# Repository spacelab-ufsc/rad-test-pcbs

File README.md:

<h1 align="center">
	RELIABILITY ENHANCED ELECTRICAL POWER SYSTEM (RE²PS) HARDWARE
	<br>
</h1>

<p align="center">

</p>

<details>
    <summary><b>Summary</b></summary>
    <ol>
        <li>
            <a href="#overview">Overview</a>
        </li>
        <li>
            <a href="#repository-organization">Repository Organization</a>
        </li>
        <li>
            <a href="#license">License</a>
        </li>
        <li>
            <a href="#releases">Releases</a>
        </li>
        <li>
            <a href="#notes">Notes</a>
        </li>
        <li>
            <a href="#references">References</a>
        </li>
    </ol>
</details>

## Overview
The PCB of **RE²PS** [[1]](#1) was designed to be more reliable than previous EPS models developed by SpaceLab. To achieve this, ECSS standards for PCB development in space environments were tailored for the project [[2]](#2). Some flexibility was applied in selecting new connectors for interfacing with other modules, but whenever possible, previously used connectors, such as Pico-Locks and PicoBlades, were chosen.

<!-- 

-->

<p align="center">

</p>

## Repository Organization
`sources`: Main files of the RE²PS's hardware project.

`outputs`: Output files, such as figures of the RE²PS's PCB, schematics, BOM and more.

## License
This project is open-source under the following license: CERN Open Hardware License v2.0.

## Releases

Releases are published after  ensuring that the project itself do not have any major errors and after testing the PCB. Please refer to the **documentation** for more details.

## Notes
For more info about the SpaceLab, access our [GitHub](https://github.com/spacelab-ufsc/spacelab), [Linkedin](https://br.linkedin.com/company/spacelab-ufsc) or our [website](https://spacelab.ufsc.br/en/home/).

## References
<a id="1">[1]</a> D. L. Figueiredo, "Reliability Enhanced Electrical Power System for Nanosatellites," in <i>Repositório Institucional da UFSC</i>, pp. 1-85, 2023, available at <a href="https://repositorio.ufsc.br/bitstream/handle/123456789/247559/PEEL2103-D.pdf?sequence=1&isAllowed=y"> this link</a>.

<a id="2">[2]</a> C. A. Rigo, L. O. Seman, M. D. Berejuck and E. A. Bezerra, "Printed Circuit Board Design Methodology for Embedded Systems Targeting Space Applications," in IEEE Latin America Transactions, vol. 18, no. 02, pp. 257-264, 2020, available at <a href="https://ieeexplore.ieee.org/document/9085278"> this link</a>.

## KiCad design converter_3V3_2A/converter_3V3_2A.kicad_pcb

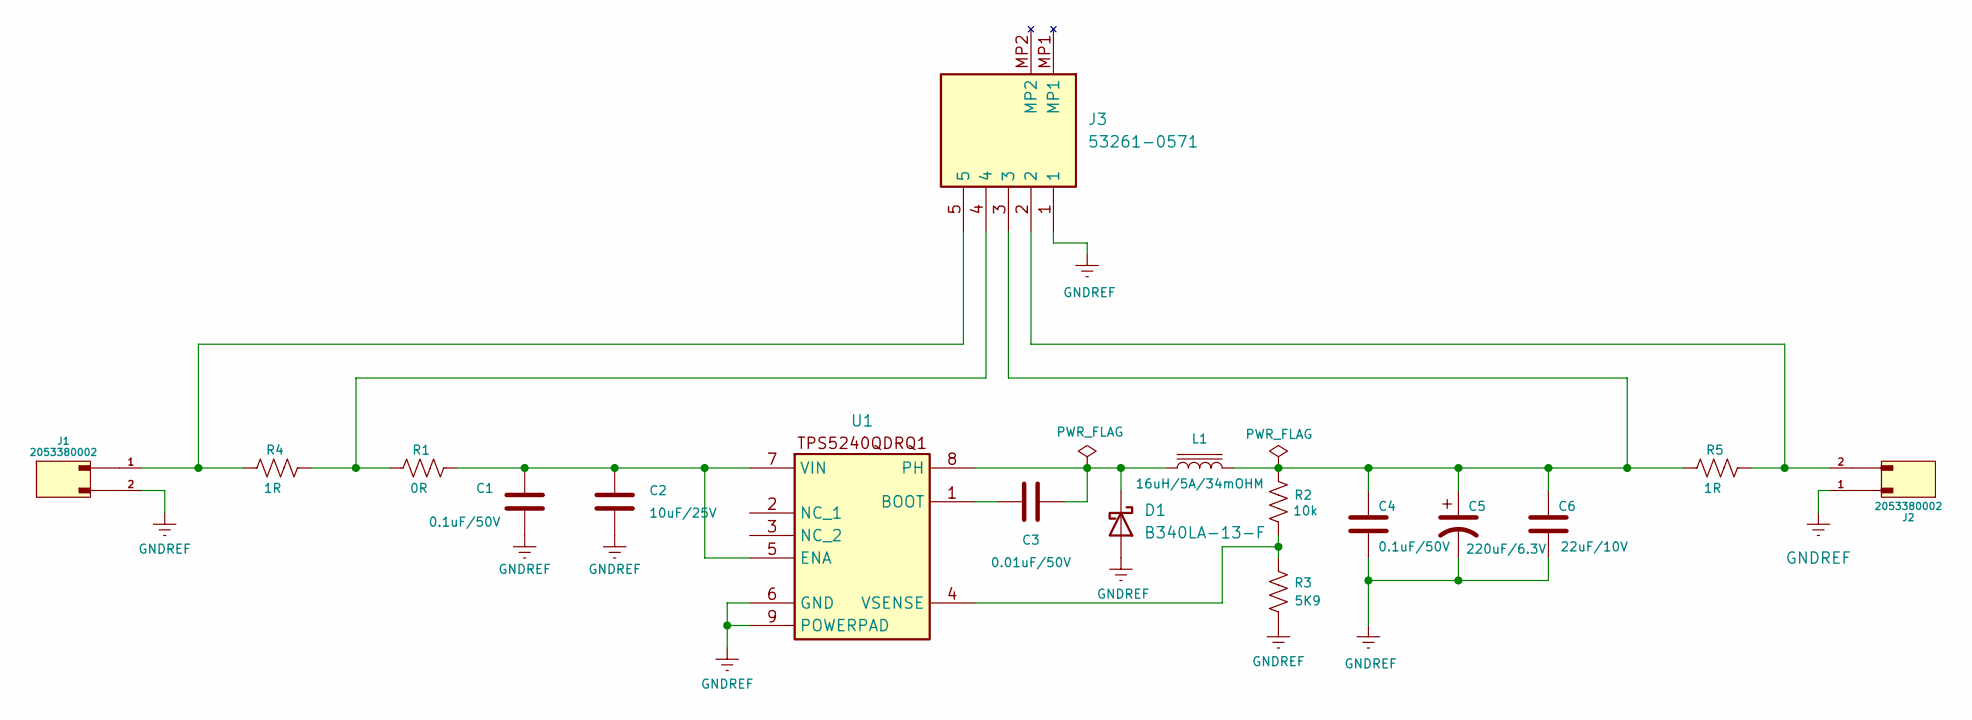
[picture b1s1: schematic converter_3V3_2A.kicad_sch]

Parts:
C1, C4: 0.1uF/50V; C_1206_3216Metric
C2: 10uF/25V; C_1206_3216Metric
C3: 0.01uF/50V; C_1206_3216Metric
C5: 220uF/6.3V; C_1206_3216Metric
C6: 22uF/10V; C_1206_3216Metric
D1: B340LA-13-F; DIOM5226X240N
J1, J2: 2053380002; MPN 2053380002
J3: 53261-0571; 532610571TR250; Mouser Part Number 538-53261-0571
L1: 16uH/5A/34mOHM; WE-HCI_105023
R1: 0R; R_0805_2012Metric_Pad1.20x1.40mm_HandSolder
R2: 10k; R_0805_2012Metric_Pad1.20x1.40mm_HandSolder
R3: 5K9; R_0805_2012Metric_Pad1.20x1.40mm_HandSolder
R4, R5: 1R; R_0805_2012Metric_Pad1.20x1.40mm_HandSolder
U1: TI_SO-PowerPAD-8

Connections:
GNDREF: C1.2, C2.2, C4.2, C5.2, C6.2, D1.2 (A), J1.2, J2.1, J3.1, R3.2, U1.6 (GND), U1.9 (POWERPAD)
unnamed: C4.1, C5.1, C6.1, J3.3, L1.2, R2.1, R5.1
unnamed: C3.2, D1.1 (K), L1.1, U1.8 (PH)
unnamed: J1.1, J3.5, R4.1
unnamed: J2.2, J3.2, R5.2
unnamed: J3.4, R1.1, R4.2
unnamed: C3.1, U1.1 (BOOT)
unnamed: C1.1, C2.1, R1.2, U1.5 (ENA), U1.7 (VIN)
unnamed: R2.2, R3.1, U1.4 (VSENSE)

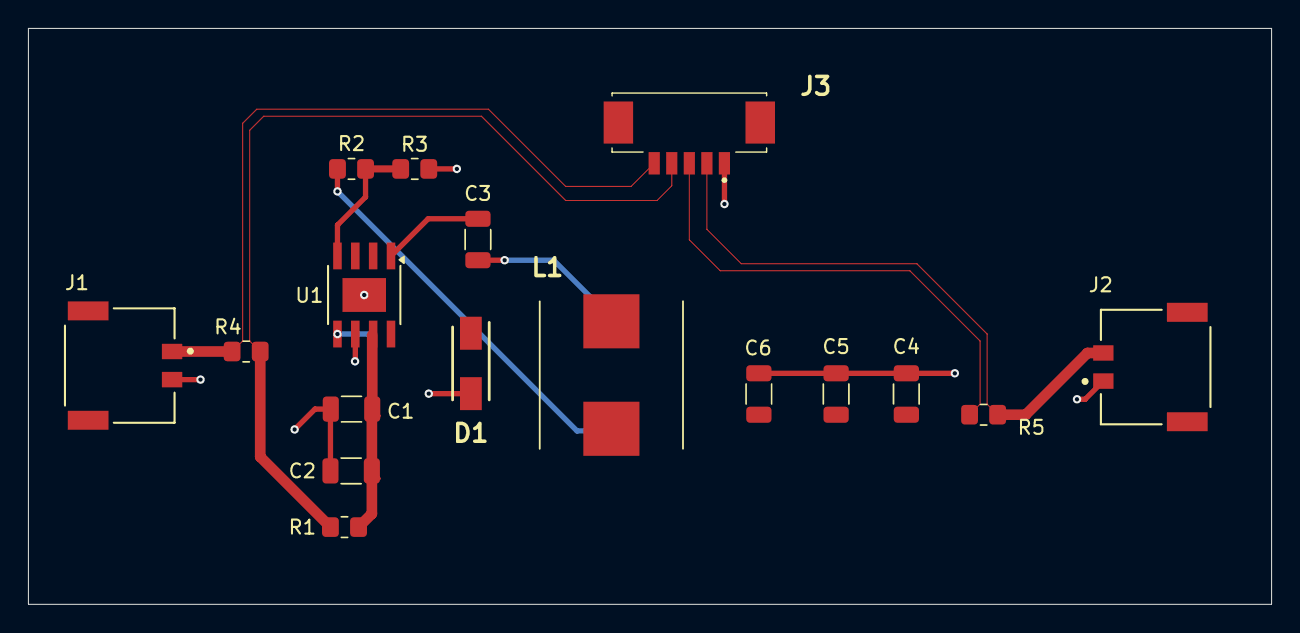
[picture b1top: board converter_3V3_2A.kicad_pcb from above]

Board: 2 copper layers, 88.5 x 41.0 mm, 17 parts (0 on the bottom side), 9 nets.

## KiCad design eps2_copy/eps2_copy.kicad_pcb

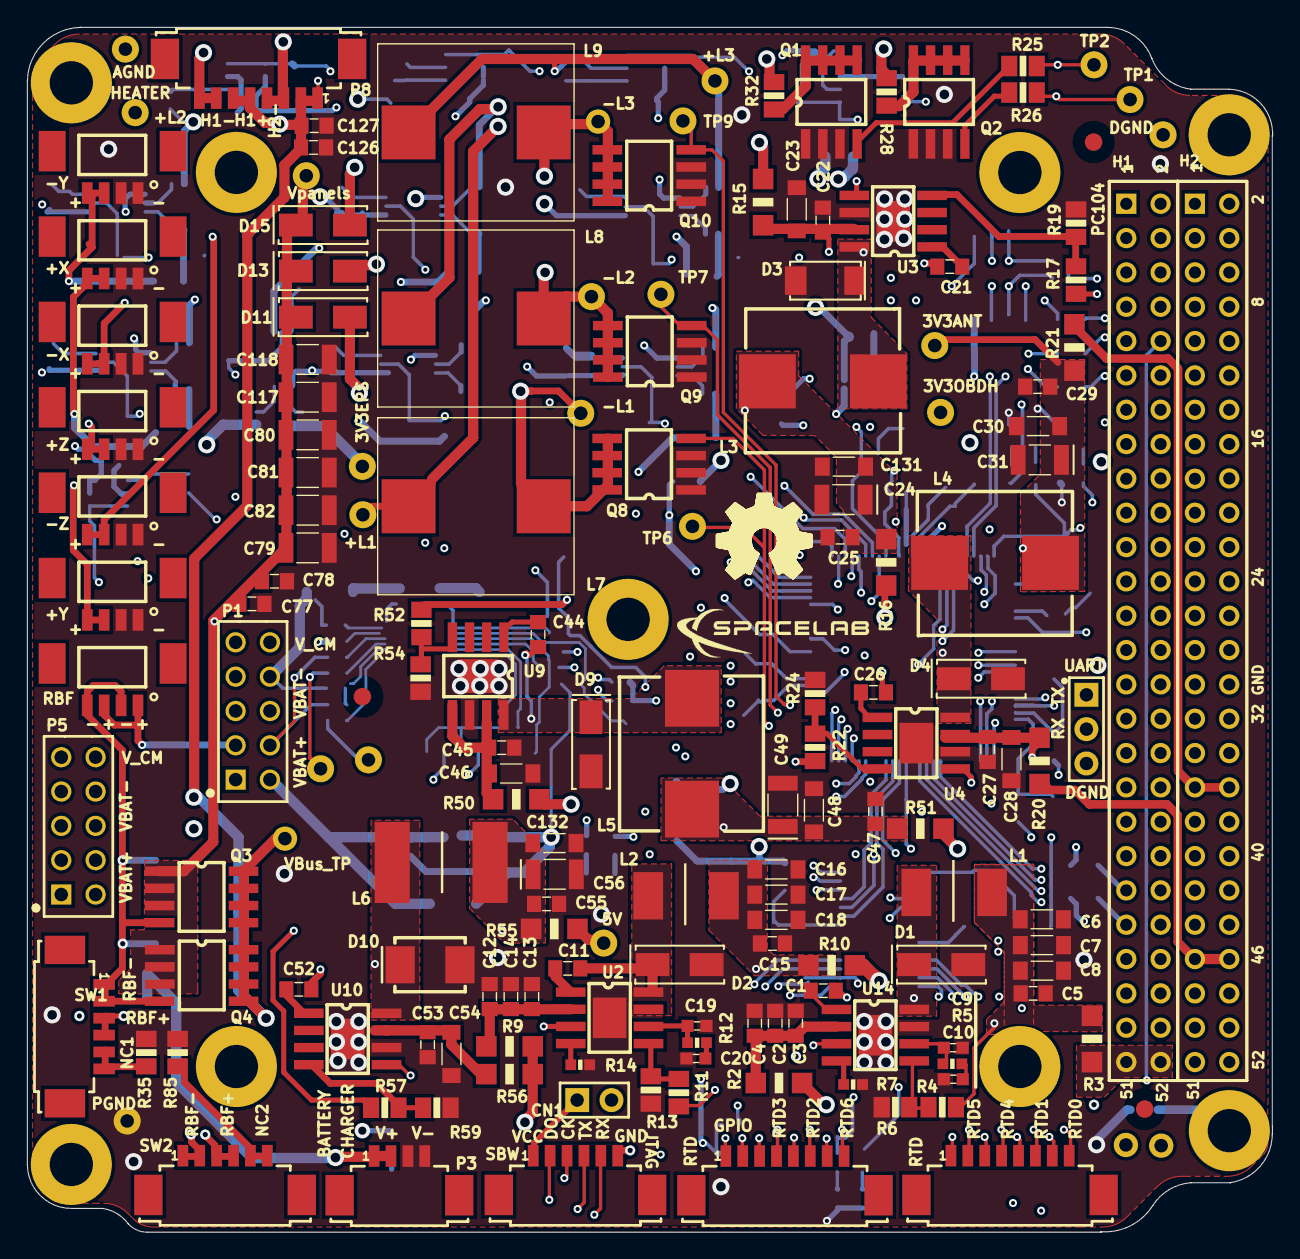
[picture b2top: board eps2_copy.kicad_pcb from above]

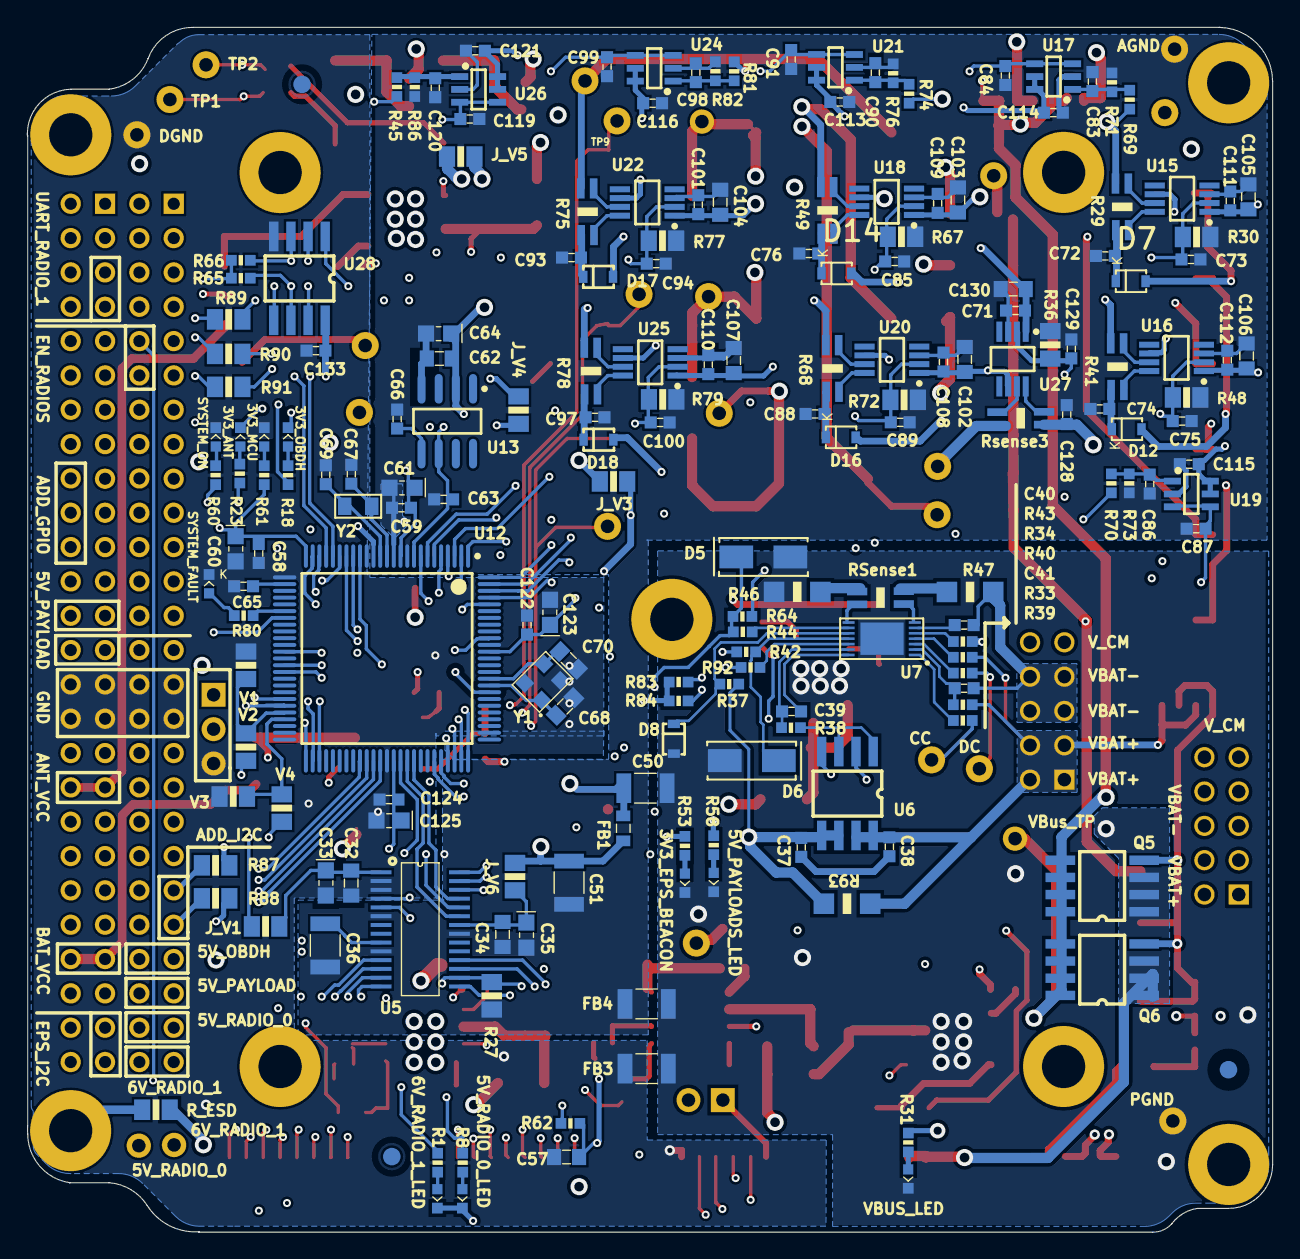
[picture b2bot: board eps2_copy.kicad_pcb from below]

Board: 4 copper layers, 92.1 x 89.1 mm, 362 parts (193 on the bottom side), 207 nets.

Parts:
3V3ANT, 3V3EPS, 3V3OBDH, 5V, 5V_RADIO_0, 6V_RADIO_1: TEST_POINT
3V3_ANT, 3V3_EPS_BEACON, 3V3_MCU, 3V3_OBDH, 5V_PAYLOADS_LED, 5V_RADIO_0_LED, 6V_RADIO_1_LED: DNP; 0603-LED
+L1, +L2, +L3: TEST_POINT
+X: Header 4_PicoBlade; HDR4 PicoBlade
+Y: Header 4_PicoBlade; HDR4 PicoBlade
+Z: Header 4_PicoBlade; HDR4 PicoBlade
-L1, -L2, -L3: TEST_POINT
-X: Header 4_PicoBlade; HDR4 PicoBlade
-Y: Header 4_PicoBlade; HDR4 PicoBlade
-Z: Header 4_PicoBlade; HDR4 PicoBlade
C1, C2, C5, C11, C12, C15, C22, C25, C27, C29, C45, C47, C53, C55, C62, C77, C78, C126, C127: 0.1uF/50V; CC0805
C3, C4, C13, C14, C102, C103, C104, C105, C106, C107, C130: 4.7uF/25V; CC0805
C6, C7, C8, C16, C17, C18, C30, C48, C131, C132: 22uF/10V; CC1206
C9, C19: 13pF/50V; CC0603
C10, C20: 5.6nF/100V; CC0603
C21, C26, C32, C34, C44, C52: 0.01uF/50V; CC0805
C23, C28, C46, C54: 10uF/25V; CC1206
C24, C31, C49, C56: 220uF/6.3V; cc1210
C33, C35, C60, C61, C64, C123, C125: 10uF/10V; CC0805_Tantalum
C36, C50, C51, C79, C80, C81, C82, C117, C118: 22uF/25V; CC1210
C37, C38: 1000pF/50V; CC0603
C39, C65: 0.47uF/50V; CC0603
C40, C41, C58, C59, C63, C71, C72, C73, C74, C75, C76, C83, C84, C85, C86, C87, C88, C89, C90, C91, C93, C94, C97, C98, C99, C100, C101, C108, C109, C110, C111, C112, C113, C114, C115, C116, C119, C120, C121, C122, C124, C128, C129, C133: 0.1uF/50V; CC0603
C57: 1nF/16V; CC0805
C66: 0.01uF/25V; CC0603
C67, C69: 12pF/50V; CC0603
C68, C70: 10pF/100V; CC0805
CC: TEST_POINT
CN1: 826646-2; HDR 1X2
D1, D2: FSV530AF; DO-214AC
D3: CMS06(TE12L,Q,M); cms06
D4, D9, D11, D13, D15: B340LA-13-F; DO-214AC
D5, D6: 3SMAJ5919B-TP; DO-214AC
D7, D8, D12, D14, D16, D17, D18: DNP; SOD323F
D10: B220-13-F; DO-214AA
DC: TEST_POINT
FB1: 30R@100Mhz, 3A; IND0805
FB3, FB4: 30R@100Mhz, 10A; IND1210
FD1, FD2, FD3, FD4, FD5, FD6: Fiducial 1.3; Fiducial 1.3mm
J_V1, J_V3, J_V4, J_V5, J_V6: 0R; 0805
L1, L2: 2.2uH/9A 15mOHM; Ind_SRP6540
L3: 27uH/4.3A/42.5mOHM; IND_744325xxx
L4, L5: 16uH/5A/34.5mOHM; IND_744325xxx
L6: 10uH/6.4A/51.8mOHM; Ind_IHLP
L7, L8, L9: 22uH/6.3/25.7mOHM; IND_HC9
MEC1, MEC2, MEC3, MEC4, MEC5, MEC6, MEC7, MEC8, MEC9: M3; M3 hole
P1, P5: Header 5X2IPS1-105-01-S-D; IPS1-105-01-S-D
P3: 0532610471; PICOBLADE 4PIN RIGHT ANGLE
P8: 0532610871; PICOBLADE 8PIN RIGHT ANGLE
PC104: PC104
Q1, Q2, Q8, Q9, Q10: MOSFET-N; SOIC8_Mosfet
Q3, Q4, Q5, Q6: MOSFET-P-SI4403CDY-T1-GE3; SOIC8_Mosfet
R1, R8, R18, R23, R31, R34, R37, R39, R40, R43, R53, R58, R60, R61: 1k; 0603
R2, R3, R9, R10, R15, R16, R20, R21, R46, R47, R50, R51, R55, R56, R93: 0R; 1206
R4: 75k; 0805
R5, R12: 19.6k; 0603
R6, R13: 11.5k; 0805
R7, R14: 140k; 0603
R11: 60.4k; 0805
R17, R22, R52, R57: 10k; 0805
R19, R24, R54: 5K9; 0805
R25, R26: 1k; 0805
R27: 1.65K; 0805
R28, R32, R87, R88, R89, R90, R91: 0R; 0805
R29, R41, R49, R68, R75, R78: 0.02R/0.5W; 1206 - ohmite
R30, R48, R67, R72, R77, R79: 3k3; R0805
R33, R42, R44: 150R; 0603
R35, R85: 100K 1/10W; 0805
R36: 4.02K; 0805
R38: 470R; 0603
R45, R70: 300K; 0603
R59: 3.24k 1/8W; 0805
R62: 47k; 0603
R64: 4K7; 0603
R65, R66, R83, R84: 10k; R0603
R69, R74, R81: 93K1; 0603
R71, R73, R76, R82, R86: 100K; 0603
R80: 1k; R0603
R92: 150R; R0603
RBF: 0533980471; PICOBLADE 4PIN VERTICAL
RSense1: 0.01R/0.5W; 1206 - ohmite
RTD1, RTD2: 0532610871; PICOBLADE 8PIN RIGHT ANGLE
R_ESD: 1.2M; 0805
Rsense3: 0.075R/0.5W; 1206 - ohmite
SBW: 0532610671; PICOBLADE 6PIN Right Angle
SW1, SW2: 0532610671; PICOBLADE 6PIN Right Angle
SYSTEM_FAULT: 150060RS75000; 0603-RED-LED
SYSTEM_ON: RED; 0603-LED
TP1, TP2, TP6, TP7, TP9: TEST_POINT
U2, U14: TPS54540QDDARQ1; SO8 Power PAD
U3: TPS5410QDRQ1; SO8 Power PAD
U4, U9: TPS5420QDRQ1; SO8 Power PAD
U5: ADS1248IPW; TSSOP28
U6: FDS6898AZ; SOIC8
U7: DS2777G+; TDFN-14-EP_3x5
U10: TPS5430QDDARQ1; SO8 Power PAD
U12: MSP430F6659IPZR; PZ0100A_N
U13: REF5025AQDRQ1; SOIC-8
U15, U16, U18, U20, U22, U25, U27: MAX9934TAUA+; MSOP-8
U17, U19, U21, U24, U26: TLV341AIDBVR; SOT-23 6L
U28: TCA4311ADR; SOIC8
UART: DNP; HDR 1X3
V1, V2, V3, V4: 47k; 0805
VBUS_LED: DNP; 0603-LED
VBus_TP: TEST_POINT
Vpanels: TEST_POINT
Y1: 32MHz 10ppm; XTAL_ABM8X
Y2: 32.768kHz 12.5pF; ABS06 0805

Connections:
3V3_DEPLOYMENT_ANT: PC104.H2-35, PC104.H2-36, R21.1
3V3_EPS_BEACON: 3V3EPS.1, C50.1, FB1.1, J_V1.2, J_V3.2, PC104.H2-27, PC104.H2-28, Rsense3.2
3V3_HEATER: C32.1, C33.1, J_V1.1, U5.1
3V3_M: C71.2, C101.2, C102.1, C103.1, C104.1, C105.1, C106.1, C107.1, C108.2, C109.2, C110.2, C111.2, C112.2, C113.2, C114.2, C115.2, C116.2, C121.2, C130.1, J_V5.1, U15.1, U15.6, U16.1, U16.6, U17.5, U17.6, U18.1, U18.6, U19.5, U19.6, U20.1, U20.6, U21.5, U21.6, U22.1, U22.6, U24.5, U24.6, U25.1, U25.6, U26.5, U26.6, U27.1, U27.6
3V3_MCU: C58.1, C60.1, C122.1, C123.1, C124.1, C125.1, C133.1, CN1.2, J_V3.1, R61.2, R62.2, R64.1, R65.1, R66.1, R83.1, R84.1, U12.25, U12.64, U12.89, U28.8, V2.1, V4.1
3V3_OBDH: PC104.H1-45, PC104.H1-46, R16.1
5V_PAYLOAD: 5V.1, PC104.H1-47, PC104.H1-48, PC104.H2-25, PC104.H2-26, R55.1
5V_Radio_0: 5V_RADIO_0.1, PC104.H1-49, PC104.H1-50, R10.1
6V_Radio_1: 6V_RADIO_1.1, PC104.H1-51, PC104.H1-52, R3.1
+RBF: C38.2, P1.1, P1.2, P1.3, P1.4, P5.1, P5.2, P5.3, P5.4, R33.1, R34.2, R93.1, RBF.1, RBF.3, SW1.3, SW1.4, SW2.3, SW2.4, U6.7, U6.8
-HEATER1_VOLTAGE: P8.7, P8.8, R32.1
-HEATER2_VOLTAGE: P8.3, P8.4, R28.1
-RBF: Q3.2, Q4.2, Q5.2, Q6.2, RBF.2, RBF.4, SW1.1, SW1.2, SW2.1, SW2.2
-VBAT: C40.2, C41.2, P1.5, P1.6, P1.7, P1.8, P5.5, P5.6, P5.7, P5.8, R47.1
A3V3_EPS: C51.1, C59.1, C61.1, C62.2, C64.1, FB1.2, J_V4.2, J_V5.2, J_V6.2, U12.11, U13.2
A3V3_HEATER: C34.1, C35.1, J_V6.1, U5.22
ADC1_I: C73.1, R30.2, U12.97, U15.2
ADC1_V: C84.2, U12.5, U17.3, U17.4
ADC2_I: C75.1, R48.2, U12.98, U16.2
ADC2_V: C91.2, U12.6, U21.3, U21.4
ADC3_I: C85.1, R67.2, U12.99, U18.2
ADC3_V: C99.2, U12.7, U24.3, U24.4
ADC4_I: C89.1, R72.2, U12.100, U20.2
ADC5_I: C94.1, R77.2, U12.1, U22.2
ADC6_I: C100.1, R79.2, U12.2, U25.2
ADC7_I: C129.1, R36.2, U12.3, U27.2
ADC_BUS: C119.2, U12.4, U26.3, U26.4
ADC_TOTAL_V: C87.2, U12.8, U19.3, U19.4
ADD_I2C1_SCL_BUF: PC104.H1-43, R88.1
ADD_I2C1_SDA_BUF: PC104.H1-41, R87.1
ADD_PC104_GPIO0: PC104.H2-18, R89.1
ADD_PC104_GPIO1: PC104.H2-20, R90.1
ADD_PC104_GPIO2: PC104.H2-22, R91.1
AGND: C34.2, C35.2, C36.2, C51.2, C59.2, C61.2, C62.1, C63.2, C64.2, C66.2, C71.1, C72.1, C73.2, C74.1, C75.2, C76.1, C83.1, C84.1, C85.2, C86.1, C87.1, C88.1, C89.2, C90.1, C91.1, C93.1, C94.2, C97.1, C98.1, C99.1, C100.2, C101.1, C102.2, C103.2, C104.2, C105.2, C106.2, C107.2, C108.1, C109.1, C110.1, C111.1, C112.1, C113.1, C114.1, C115.1, C116.1, C119.1, C120.1, C121.1, C128.1, C129.2, C130.2, FB4.1, R27.1, R30.1, R36.1, R48.1, R67.1, R71.1, R72.1, R73.1, R76.1, R77.1, R79.1, R82.1, R86.1, U5.6, U5.10, U5.21, U12.10, U12.12, U12.15, U12.83, U13.4, U15.3, U16.3, U17.2, U18.3, U19.2, U20.3, U21.2, U22.3, U24.2, U25.3, U26.2, U27.3
BAT_GPIO1: RTD1.1, U12.39
BAT_GPIO2: RTD1.2, U12.40
DGND: 3V3_MCU.2, C32.2, C33.2, C57.2, C58.2, C60.2, C65.2, C67.2, C68.2, C69.2, C70.2, C122.2, C123.2, C124.2, C125.2, C133.2, FB3.1, PC104.H1-29, PC104.H1-30, PC104.H1-31, PC104.H1-32, PC104.H2-29, PC104.H2-30, PC104.H2-31, PC104.H2-32, SBW.6, SYSTEM_FAULT.2, SYSTEM_ON.2, U5.2, U5.3, U12.26, U12.63, U12.90, U28.4, UART.3, V1.2, V3.2, Y1.2, Y1.4
EN_PAYLOAD: U10.5, U12.37
ESD: MEC4.0, R_ESD.2
En_5V_Radio_0: PC104.H1-12, U2.3
En_6V_Radio_1: PC104.H1-10, U14.3
HEATER1_PWM: R25.2, TP2.1, U12.45
HEATER2_PWM: R26.2, TP1.1, U12.44
I2C0_SCL: R84.2, R92.1, U12.19
I2C0_SDA: R42.2, R83.2, U12.18
I2C1_EN: U12.72, U28.1
I2C1_READY: U12.75, U28.5
I2C1_SCL: R66.2, U12.74, U28.3
I2C1_SCL_BUF: PC104.H2-51, R88.2, U28.2
I2C1_SDA: R65.2, U12.73, U28.6
I2C1_SDA_BUF: PC104.H2-49, R87.2, U28.7
JTAG_VCC: CN1.1, SBW.1
MPPT_PWM_1: Q8.2, TP6.1, U12.51
MPPT_PWM_2: Q9.2, TP7.1, U12.52
MPPT_PWM_3: Q10.2, TP9.1, U12.53
NC_KILL_SWITCH1: R35.1, SW1.5, SW1.6
NC_KILL_SWITCH2: R85.1, SW2.5, SW2.6
Net3V3ANT_1: 3V3ANT.1, C29.1, C30.1, C31.1, L4.2, R21.2, R22.2, R23.1
Net3V3OBDH_1: 3V3OBDH.1, C24.1, C25.1, C131.1, L3.2, R16.2, R17.2, R18.1
Net3V3_ANT_1: 3V3_ANT.1, R23.2
Net3V3_EPS_BEACON_1: 3V3_EPS_BEACON.1, R53.1
Net3V3_MCU_1: 3V3_MCU.1, R61.1
Net3V3_OBDH_1: 3V3_OBDH.1, R18.2
Net5V_PAYLOADS_LED_1: 5V_PAYLOADS_LED.1, R58.2
Net5V_RADIO_0_LED_1: 5V_RADIO_0_LED.1, R8.2
Net6V_RADIO_1_LED_1: 6V_RADIO_1_LED.1, R1.2
Net+L1_1: +L1.1, L7.1, R29.2, R41.2, R69.2
Net+L2_1: +L2.1, L8.1, R49.2, R68.2, R74.2
Net+L3_1: +L3.1, L9.1, R75.2, R78.2, R81.2
Net-L1_1: -L1.1, D11.2, L7.2, Q8.3
Net-L2_1: -L2.1, D13.2, L8.2, Q9.3
Net-L3_1: -L3.1, D15.2, L9.2, Q10.3
NetC1_1: C1.1, U14.1
NetC1_2: C1.2, D1.1, L1.1, U14.8
NetC2_1: C2.1, C3.1, C4.1, R2.1, U14.2
NetC5_1: C5.1, C6.1, C7.1, C8.1, L1.2, R1.1, R3.2, R4.2
NetC9_1: C9.1, R5.2, U14.6
NetC10_1: C10.1, R5.1
NetC11_1: C11.1, U2.1
NetC11_2: C11.2, D2.1, L2.1, U2.8
NetC12_1: C12.1, C13.1, C14.1, R9.1, U2.2
NetC15_1: C15.1, C16.1, C17.1, C18.1, L2.2, R8.1, R10.2, R11.2
NetC19_1: C19.1, R12.2, U2.6
NetC20_1: C20.1, R12.1
NetC21_1: C21.1, U3.1
NetC21_2: C21.2, D3.1, L3.1, U3.8
NetC22_1: C22.1, C23.1, R15.1, U3.5, U3.7
NetC26_1: C26.1, U4.1
NetC26_2: C26.2, D4.1, L4.1, U4.8
NetC27_1: C27.1, C28.1, R20.1, U4.5, U4.7
NetC36_1: C36.1, U5.9
NetC37_2: C37.2, C38.1
NetC39_1: C39.1, U7.14
NetC40_1: C40.1, U7.6
NetC41_1: C41.1, R33.2, U7.2
NetC44_1: C44.1, U9.1
NetC44_2: C44.2, D9.1, L5.1, U9.8
NetC45_2: C45.2, C46.1, R50.1, U9.5, U9.7
NetC47_2: C47.2, C48.1, C49.1, L5.2, R51.2, R52.2, R53.2
NetC52_1: C52.1, U10.1
NetC52_2: C52.2, D10.1, L6.1, U10.8
NetC53_1: C53.1, C54.1, R56.1, U10.7
NetC55_1: C55.1, C56.1, C132.1, L6.2, R55.2, R57.2, R58.1
NetC65_1: C65.1, U12.27
NetC66_1: C66.1, U13.5
NetC72_2: C72.2, D7.1, R29.1
NetC74_2: C74.2, D12.1, R41.1
NetC76_2: C76.2, D14.1, R49.1
NetC83_2: C83.2, R69.1, R71.2, U17.1
NetC86_2: C86.2, R70.1, R73.2, U19.1
NetC88_2: C88.2, D16.1, R68.1
NetC90_2: C90.2, R74.1, R76.2, U21.1
NetC93_2: C93.2, D17.1, R75.1
NetC97_2: C97.2, D18.1, R78.1
NetC98_2: C98.2, R81.1, R82.2, U24.1
NetC120_2: C120.2, R45.1, R86.2, U26.1
NetC128_2: C128.2, R51.1, Rsense3.1
NetCC_1: CC.1, R39.2, U6.4
NetD6_1: D6.1, R42.1, U7.11
NetD8_1: D8.1, R37.1, U7.10
NetDC_1: DC.1, R40.2, U6.2
NetQ1_2: Q1.2, R25.1
NetQ1_3: Q1.3, R32.2
NetQ2_2: Q2.2, R26.1
NetQ2_3: Q2.3, R28.2
NetR4_1: R4.1, R6.2, U14.5
NetR7_2: R7.2, U14.4
NetR11_1: R11.1, R13.2, U2.5
NetR14_2: R14.2, U2.4
NetR17_1: R17.1, R19.2, U3.4
NetR22_1: R22.1, R24.2, U4.4
NetR31_2: R31.2, VBUS_LED.1
NetR34_1: R34.1, U7.4
NetR38_2: R38.2, U6.1, U6.3
NetR39_1: R39.1, U7.1
NetR40_1: R40.1, U7.3
NetR43_2: R43.2, U7.5
NetR44_1: R44.1, U7.9
NetR46_1: R46.1, RSense1.4
NetR47_2: R47.2, RSense1.3
NetR52_1: R52.1, R54.2, U9.4
NetR57_1: R57.1, R59.2, U10.4
NetR60_1: R60.1, SYSTEM_ON.1
NetR80_1: R80.1, SYSTEM_FAULT.1
NetR92_2: R92.2, U7.12
NetRsense3_3: Rsense3.3, U27.8
NetRsense3_4: Rsense3.4, U27.7
PANEL+X: +X.3, +X.4, D12.2
PANEL+Y: +Y.3, +Y.4, D18.2
PANEL+Z: +Z.3, +Z.4, D16.2
PANEL-X: -X.3, -X.4, D14.2
PANEL-Y: -Y.3, -Y.4, D7.2
PANEL-Z: -Z.3, -Z.4, D17.2
PC104_GPIO0: R89.2, U12.24
PC104_GPIO1: R90.2, U12.23
PC104_GPIO2: R91.2, U12.20
PGND: 3V3_ANT.2, 3V3_EPS_BEACON.2, 3V3_OBDH.2, 5V_PAYLOADS_LED.2, 5V_RADIO_0_LED.2, 6V_RADIO_1_LED.2, +X.1, +X.2, +Y.1, +Y.2, +Z.1, +Z.2, -X.1, -X.2, -Y.1, -Y.2, -Z.1, -Z.2, C2.2, C3.2, C4.2, C5.2, C6.2, C7.2, C8.2, C9.2, C10.2, C12.2, C13.2, C14.2, C15.2, C16.2, C17.2, C18.2, C19.2, C20.2, C22.2, C23.2, C24.2, C25.2, C27.2, C28.2, C29.2, C30.2, C31.2, C45.1, C46.2, C47.1, C48.2, C49.2, C50.2, C53.2, C54.2, C55.2, C56.2, C77.2, C78.2, C79.2, C80.2, C81.2, C82.2, C117.2, C118.2, C126.1, C127.1, C131.2, C132.2, D1.2, D2.2, D3.2, D4.2, D5.2, D6.2, D8.2, D9.2, D10.2, FB3.2, FB4.2, P3.3, P3.4, Q1.1, Q2.1, Q8.1, Q9.1, Q10.1, R6.1, R7.1, R13.1, R14.1, R19.1, R24.1, R35.2, R46.2, R54.1, R59.1, R85.2, R_ESD.1, U2.7, U2.9, U3.6, U3.9, U4.6, U4.9, U7.15, U9.6, U9.9, U10.6, U10.9, U14.7, U14.9, VBUS_LED.2
PIO: D5.1, R44.2, R64.2, U12.17
RTD0: RTD2.8, U5.11
RTD1: RTD2.6, U5.12
RTD2: RTD1.6, U5.17
RTD3: RTD1.4, U5.18
RTD4: RTD2.4, U5.13
RTD5: RTD2.2, U5.14
RTD6: RTD1.8, U5.15
RTD_COMMON: R27.2, RTD1.3, RTD1.5, RTD1.7, RTD2.1, RTD2.3, RTD2.5, RTD2.7, U5.5, U5.16
RTD_CS: U5.24, U12.65
RTD_DIN: U5.27, U12.60
RTD_DOUT: U5.26, U12.61
RTD_DRDY: U5.25, U12.67
RTD_RESET: U5.4, U12.62
RTD_SCLK: U5.28, U12.59
RTD_START: U5.23, U12.66
SRC: C39.2, R38.1, U7.13
SYSTEM_FAULT_LED: R80.2, U12.31
SYSTEM_ON: R60.2, U12.32
TCK: SBW.3, U12.91
TDO: C57.1, R62.1, SBW.2, U12.96
UART_DEBUG_RX: SBW.5, U12.71, UART.2
UART_DEBUG_TX: SBW.4, U12.70, UART.1
UART_EPS_RX_Beacon_TX: PC104.H2-7, U12.22
UART_EPS_TX_BEACON_RX: PC104.H2-5, U12.21
VBAT_COMMON: P1.9, P1.10, P5.9, P5.10, R43.1
VBus: C126.2, C127.2, P8.1, P8.2, P8.5, P8.6, PC104.H2-45, PC104.H2-46, Q3.3, Q4.3, Q5.3, Q6.3, R2.2, R9.2, R15.2, R20.2, R31.1, R45.2, R50.2, R56.2, VBus_TP.1
VPANELS: C77.1, C78.1, C79.1, C80.1, C81.1, C82.1, C117.1, C118.1, D11.1, D13.1, D15.1, Q3.1, Q4.1, R70.2, Vpanels.1
VREF+: C63.1, J_V4.1, U12.9, U13.6
VSENSE1_N: R29.4, U15.7
VSENSE1_P: R29.3, U15.8
VSENSE2_N: R41.4, U16.7
VSENSE2_P: R41.3, U16.8
VSENSE3_N: R49.4, U18.7
VSENSE3_P: R49.3, U18.8
VSENSE4_N: R68.4, U20.7
VSENSE4_P: R68.3, U20.8
VSENSE5_N: R75.4, U22.7
VSENSE5_P: R75.3, U22.8
VSENSE6_N: R78.4, U25.7
VSENSE6_P: R78.3, U25.8
V_CHARGING_BATTERIES: C37.1, P3.1, P3.2, Q5.1, Q6.1, R37.2, R93.2, U6.5, U6.6
V_SENSE0_N: RSense1.2, U7.8
V_SENSE0_P: RSense1.1, U7.7
Version_BIT0: U12.46, V1.1, V2.2
Version_BIT1: U12.47, V3.1, V4.2
XIN: C67.1, U12.13, Y2.1
XOUT: C69.1, U12.14, Y2.2
XT2IN: C68.1, U12.84, Y1.1
XT2OUT: C70.1, U12.85, Y1.3

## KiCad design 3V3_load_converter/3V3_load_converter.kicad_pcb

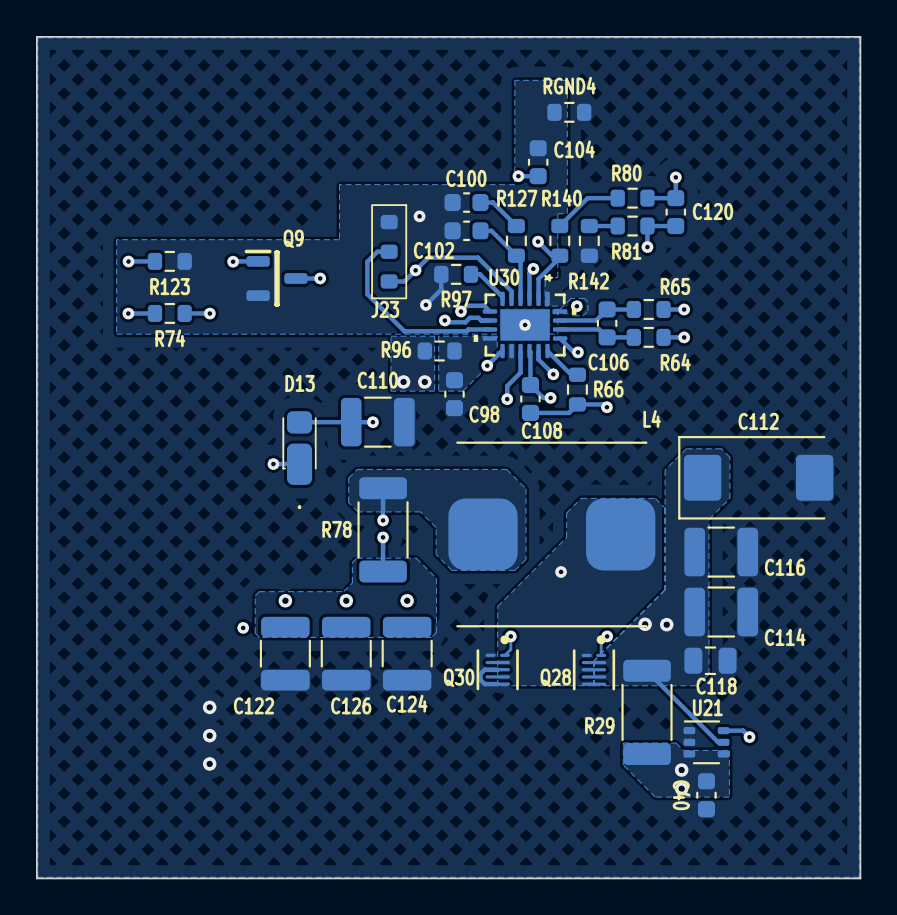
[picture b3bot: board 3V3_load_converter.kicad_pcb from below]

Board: 6 copper layers, 45.8 x 46.7 mm, 40 parts (40 on the bottom side), 27 nets.

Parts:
C40, C98, C108: 100nF; CAP0603
C100: 3.3nF; CAP0603
C102: 100pF; CAP0603
C104, C106: 1nF; CAP0603
C110: 4.7uF; CAP1210
C112: 47uF; CAP2917POL
C114, C116: 10uF; CAP1210
C118: 1uF; CAP0805
C120: 22pF; CAP0603
C122, C124, C126: 22uF; CAP1210
D13: SS12FP
J23: N/A; three_position_jumper
JP4: N/A; Jumper
L4: 2.4uH; 744325240
Q9: SI2302DDS-T1-GE3
Q28, Q30: EPC2016C
R29: 5m; RES2010
R64, R65, R66: 10R; RES0603
R74, R123: 100k; RES0603
R78: 16m; RES2010
R80, R81: 0R; RES0603
R96: 2.2R; RES0603
R97: 82k; RES0603
R127: 12k; RES0603
R140: 90.9k; RES0603
R142: 20k; RES0603
RGND4: 0R; RES0603
U21: INA199C3DCKR
U30: LTC3833EUDC#TRPBF

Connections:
+3V3: C120.2, C122.2, C124.2, C126.2, JP4.2 (B), R78.2, R80.1, U30.8 (EXTVCC), U30.20 (VOUT)
/3V3_A_~EN: Q9.1 (G), R123.2
/U_3V3_Load_Converters/3V3_SENSE1+: L4.2, R64.1, R78.1
/U_3V3_Load_Converters/3V3_SENSE1-: JP4.1 (A), R65.1
/U_3V3_Load_Converters/3V3_VCC1: C110.1, D13.2 (A), J23.1, R74.2, U30.5 (VRNG), U30.11 (INTVCC)
/U_3V3_Load_Converters/VBUS_BK3V3: C112.1, C114.2, C116.2, C118.2, Q28.3 (Drain), Q28.5 (Drain), R29.2, R96.2, U21.5 (IN-)
GNDPWR: C40.1, C98.2, C110.2, C112.2, C114.1, C116.1, C118.1, C122.1, C124.1, C126.1, Q30.2 (Substrate), Q30.4 (Source), Q30.6 (Source), R142.1, RGND4.2, U21.1 (REF), U21.2 (GND), U30.1 (VOSNS-), U30.12 (PGND)
GNDS3: C100.1, C102.1, C104.1, J23.3, Q9.2 (S), R97.1, R123.1, RGND4.1, U30.21 (EPAD)
unnamed: C100.2, R127.2
unnamed: C108.2, D13.1 (K), R66.1
unnamed: Q9.3 (D), U30.7 (RUN)
unnamed: Q28.1 (Gate), U30.15 (TG)
unnamed: C108.1, L4.1, Q28.2 (Substrate), Q28.4 (Source), Q28.6 (Source), Q30.3 (Drain), Q30.5 (Drain), U30.14 (SW)
unnamed: Q30.1 (Gate), U30.13 (BG)
unnamed: R80.2, R140.2
unnamed: R81.2, R142.2
unnamed: R66.2, U30.16 (BOOST)
unnamed: C102.2, R127.1, U30.4 (ITH)
unnamed: J23.2, U30.9 (MODE/PLLIN)
unnamed: R74.1, U30.17 (PGOOD)
unnamed: R97.2, U30.6 (RT)
unnamed: C106.2, R64.2, U30.18 (SENSE+)
unnamed: C106.1, R65.2, U30.19 (SENSE-)
unnamed: C104.2, U30.3 (TRACK/SS)
unnamed: C98.1, R96.1, U30.10 (VIN)
unnamed: C120.1, R81.1, R140.1, U30.2 (VOSNS+)
VBUS: C40.2, R29.1, U21.3 (V+), U21.4 (IN+)
